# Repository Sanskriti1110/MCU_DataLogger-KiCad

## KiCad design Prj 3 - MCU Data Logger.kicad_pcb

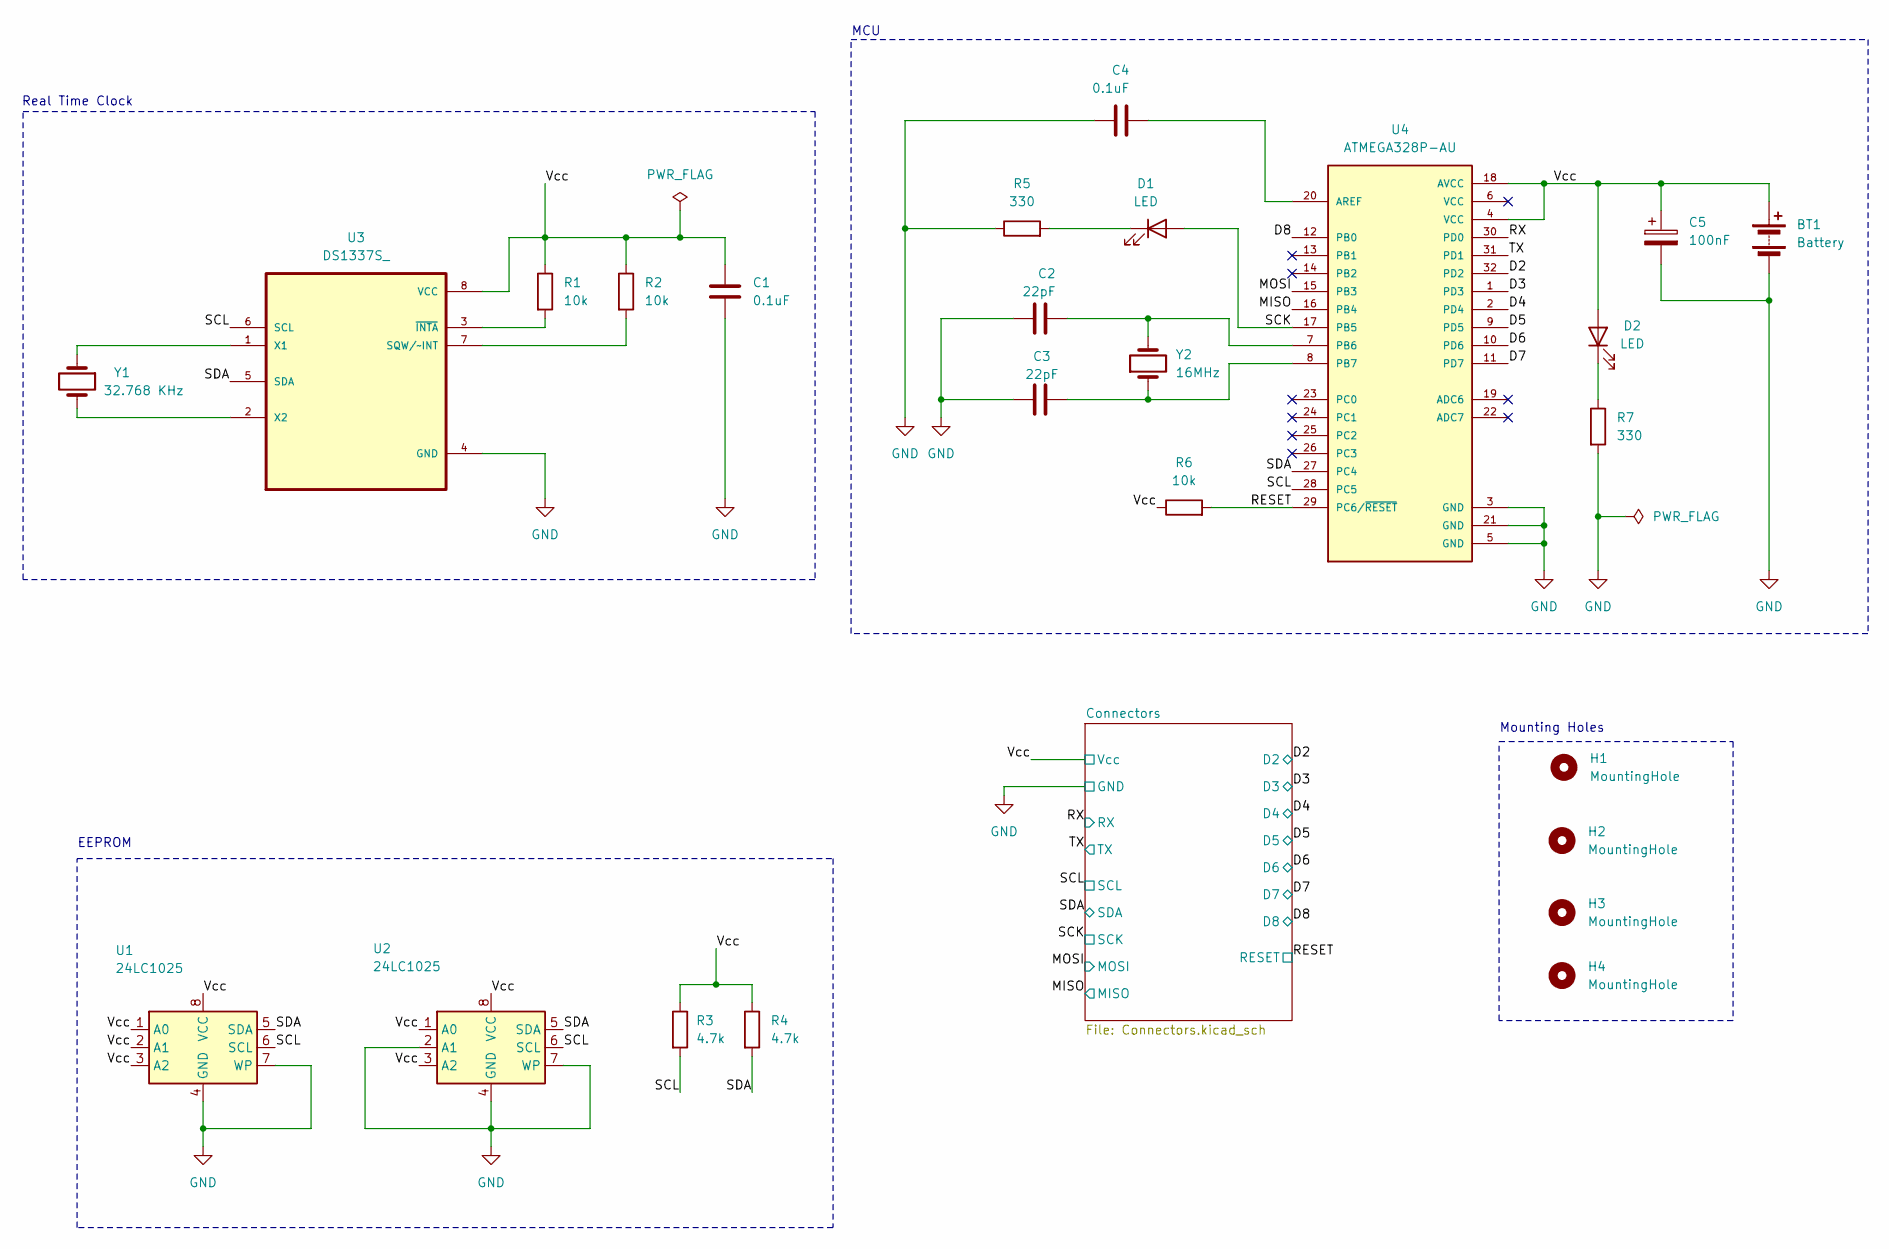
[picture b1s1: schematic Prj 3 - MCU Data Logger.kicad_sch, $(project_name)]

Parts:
BT1: Battery; PinHeader_1x02_P2.54mm_Vertical
C1, C4: 0.1uF; C_0805_2012Metric
C2, C3: 22pF; C_0805_2012Metric
C5: 100nF; C_0805_2012Metric
D1, D2: LED; LED_0805_2012Metric
H1, H2, H3, H4: MountingHole; MountingHole_2.1mm
R1, R2, R6: 10k; R_0805_2012Metric
R3, R4: 4.7k; R_0805_2012Metric
R5, R7: 330; R_0805_2012Metric
U1, U2: 24LC1025; SOIC-8_5.23x5.23mm_P1.27mm
U3: DS1337S_; DS1337S
U4: ATMEGA328P-AU; PARTREV 8271A
Y1: 32.768 KHz; Crystal_SMD_5032-2Pin_5.0x3.2mm_HandSoldering
Y2: 16MHz; Crystal_SMD_5032-2Pin_5.0x3.2mm_HandSoldering

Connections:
/D2: U4.32 (PD2); also elsewhere on the board
/D3: U4.1 (PD3); also elsewhere on the board
/D4: U4.2 (PD4); also elsewhere on the board
/D5: U4.9 (PD5); also elsewhere on the board
/D6: U4.10 (PD6); also elsewhere on the board
/D7: U4.11 (PD7); also elsewhere on the board
/D8: U4.12 (PB0); also elsewhere on the board
/MISO: U4.16 (PB4); also elsewhere on the board
/MOSI: U4.15 (PB3); also elsewhere on the board
/RESET: R6.2, U4.29 (PC6/~RESET); also elsewhere on the board
/RX: U4.30 (PD0); also elsewhere on the board
/SCK: D1.2 (A), U4.17 (PB5); also elsewhere on the board
/SCL: R3.2, U1.6 (SCL), U2.6 (SCL), U3.6 (SCL), U4.28 (PC5); also elsewhere on the board
/SDA: R4.2, U1.5 (SDA), U2.5 (SDA), U3.5 (SDA), U4.27 (PC4); also elsewhere on the board
/TX: U4.31 (PD1); also elsewhere on the board
/Vcc: BT1.1 (+), C1.1, C5.1, D2.2 (A), R1.1, R2.1, R3.1, R4.1, R6.1, U1.1 (A0), U1.2 (A1), U1.3 (A2), U1.8 (VCC), U2.1 (A0), U2.3 (A2), U2.8 (VCC), U3.8 (VCC), U4.4 (VCC), U4.18 (AVCC); also elsewhere on the board
GND: BT1.2 (-), C1.2, C2.1, C3.1, C4.1, C5.2, R5.1, R7.2, U1.4 (GND), U1.7 (WP), U2.2 (A1), U2.4 (GND), U2.7 (WP), U3.4 (GND), U4.3 (GND), U4.5 (GND), U4.21 (GND); also elsewhere on the board
unnamed: D1.1 (K), R5.2
unnamed: D2.1 (K), R7.1
unnamed: R2.2, U3.7 (SQW/~INT)
unnamed: U3.1 (X1), Y1.1
unnamed: U3.2 (X2), Y1.2
unnamed: R1.2, U3.3 (~INTA)
unnamed: C4.2, U4.20 (AREF)
unnamed: C2.2, U4.7 (PB6), Y2.2
unnamed: C3.2, U4.8 (PB7), Y2.1

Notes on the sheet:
EEPROM
Real Time Clock
Mounting Holes
MCU

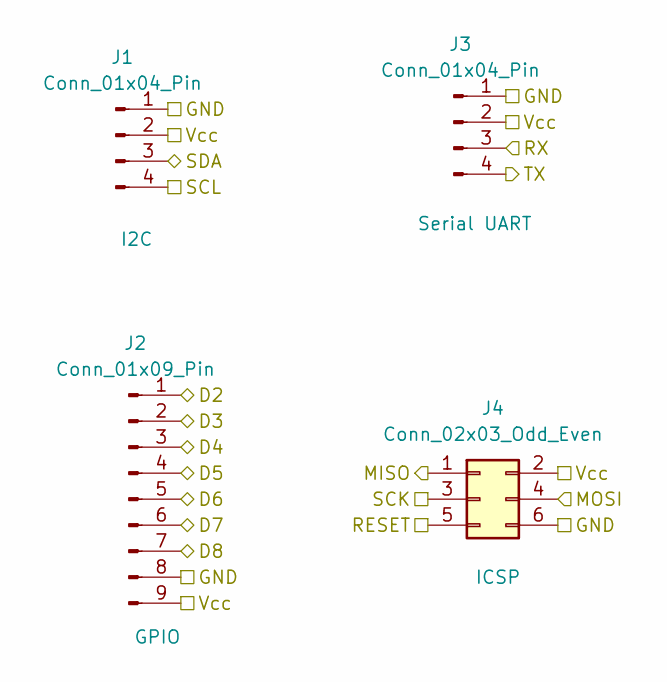
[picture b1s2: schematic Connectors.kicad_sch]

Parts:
J1, J3: Conn_01x04_Pin; PinHeader_1x04_P2.54mm_Vertical
J2: Conn_01x09_Pin; PinHeader_1x09_P2.54mm_Vertical
J4: Conn_02x03_Odd_Even; PinHeader_2x03_P2.54mm_Vertical

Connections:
/D2: J2.1; also elsewhere on the board
/D3: J2.2; also elsewhere on the board
/D4: J2.3; also elsewhere on the board
/D5: J2.4; also elsewhere on the board
/D6: J2.5; also elsewhere on the board
/D7: J2.6; also elsewhere on the board
/D8: J2.7; also elsewhere on the board
/MISO: J4.1; also elsewhere on the board
/MOSI: J4.4; also elsewhere on the board
/RESET: J4.5; also elsewhere on the board
/RX: J3.3; also elsewhere on the board
/SCK: J4.3; also elsewhere on the board
/SCL: J1.4; also elsewhere on the board
/SDA: J1.3; also elsewhere on the board
/TX: J3.4; also elsewhere on the board
/Vcc: J1.2, J2.9, J3.2, J4.2; also elsewhere on the board
GND: J1.1, J2.8, J3.1, J4.6; also elsewhere on the board

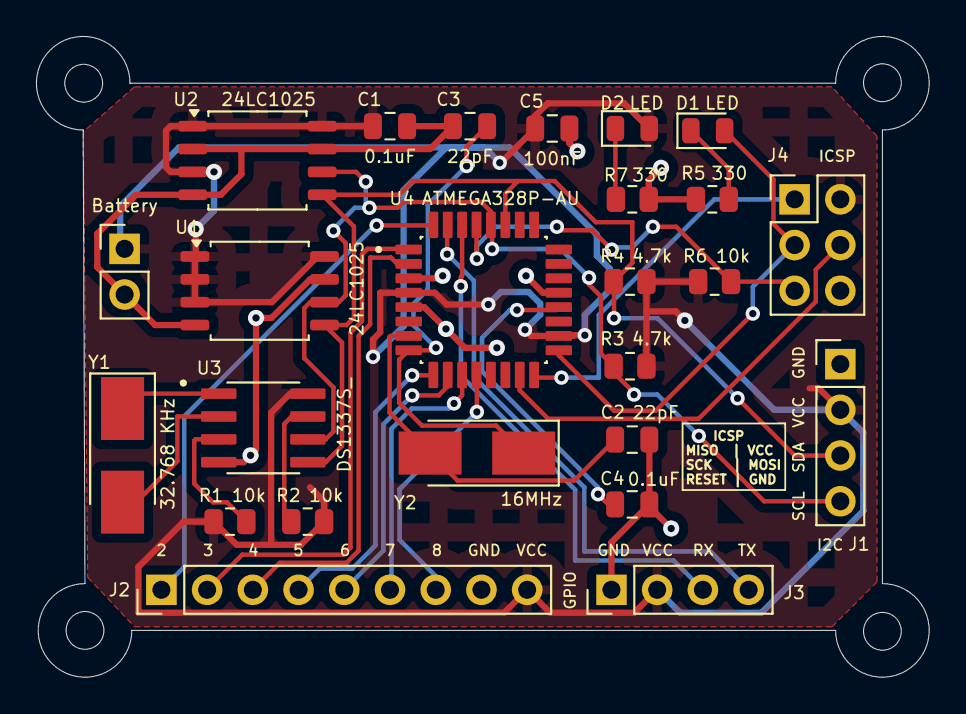
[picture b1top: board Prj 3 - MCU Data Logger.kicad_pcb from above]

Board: 2 copper layers, 49.6 x 35.6 mm, 29 parts (0 on the bottom side), 26 nets.

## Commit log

2024-05-22 setup of EESchema
2024-05-23 Have added required symbols to the schematic sheets
2024-05-23 Placed symbols and added component values
2024-05-23 add footprints to symbols
2024-05-23 Wiring completed
2024-05-23 Added nets to net Class
2024-05-23 schematic completed
2024-05-23 Setup PCB New
2024-05-27 Arranged placeholders
2024-05-27 Routing done except gnd and vcc
2024-05-27 Routing completed
2024-05-28 Fixed outstanding issues
2024-05-28 Completed 2 layer PCB Project
2024-05-28 completed 2-layer pcb design
2024-05-28 added gerber file for 4layer pcb
2024-05-28 Completed 4layer PCB
2024-05-28 Added board characteristics
2024-05-28 Added gitattributes file to preven pcb files from merge
2024-05-29 nothing much
2024-05-29 fixed 2 defects in schematic
2024-05-29 Fixed 2layer PCB
2024-05-29 Fixed all bugs in 4layer PCB
2024-05-29 generated gerber files
2024-05-29 Generated gerber files for 2layer
